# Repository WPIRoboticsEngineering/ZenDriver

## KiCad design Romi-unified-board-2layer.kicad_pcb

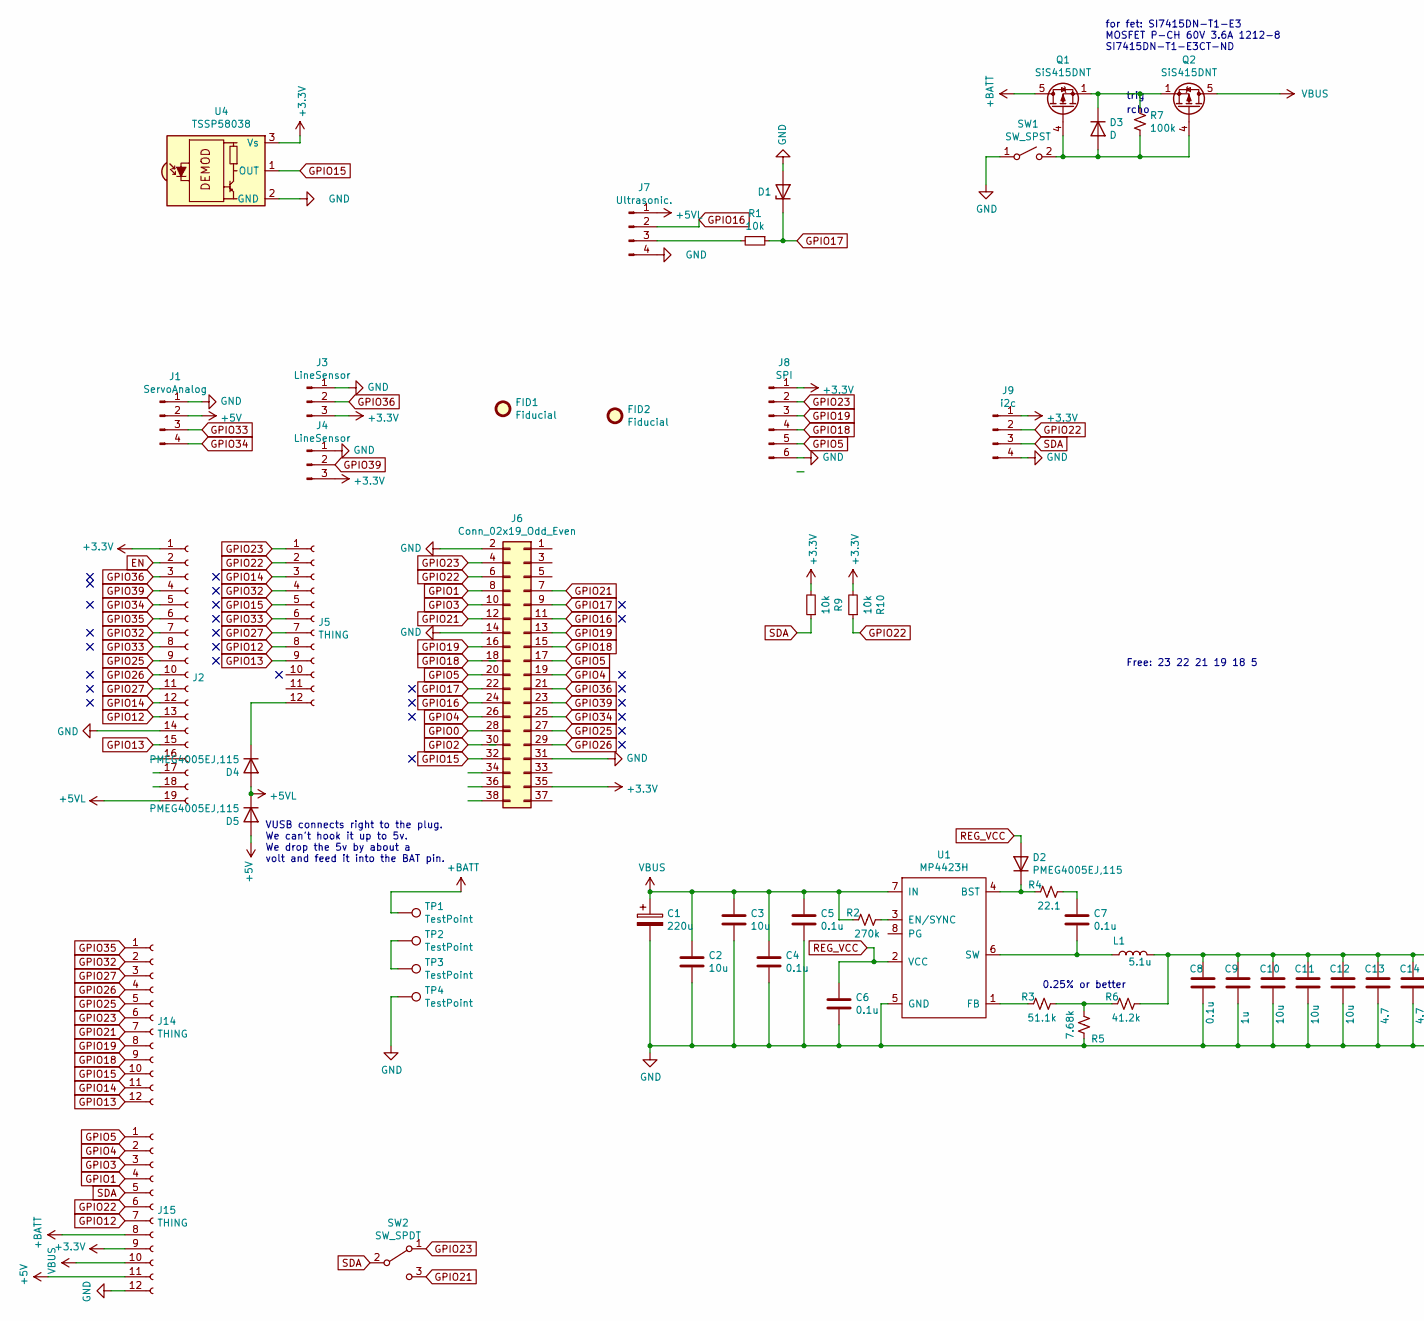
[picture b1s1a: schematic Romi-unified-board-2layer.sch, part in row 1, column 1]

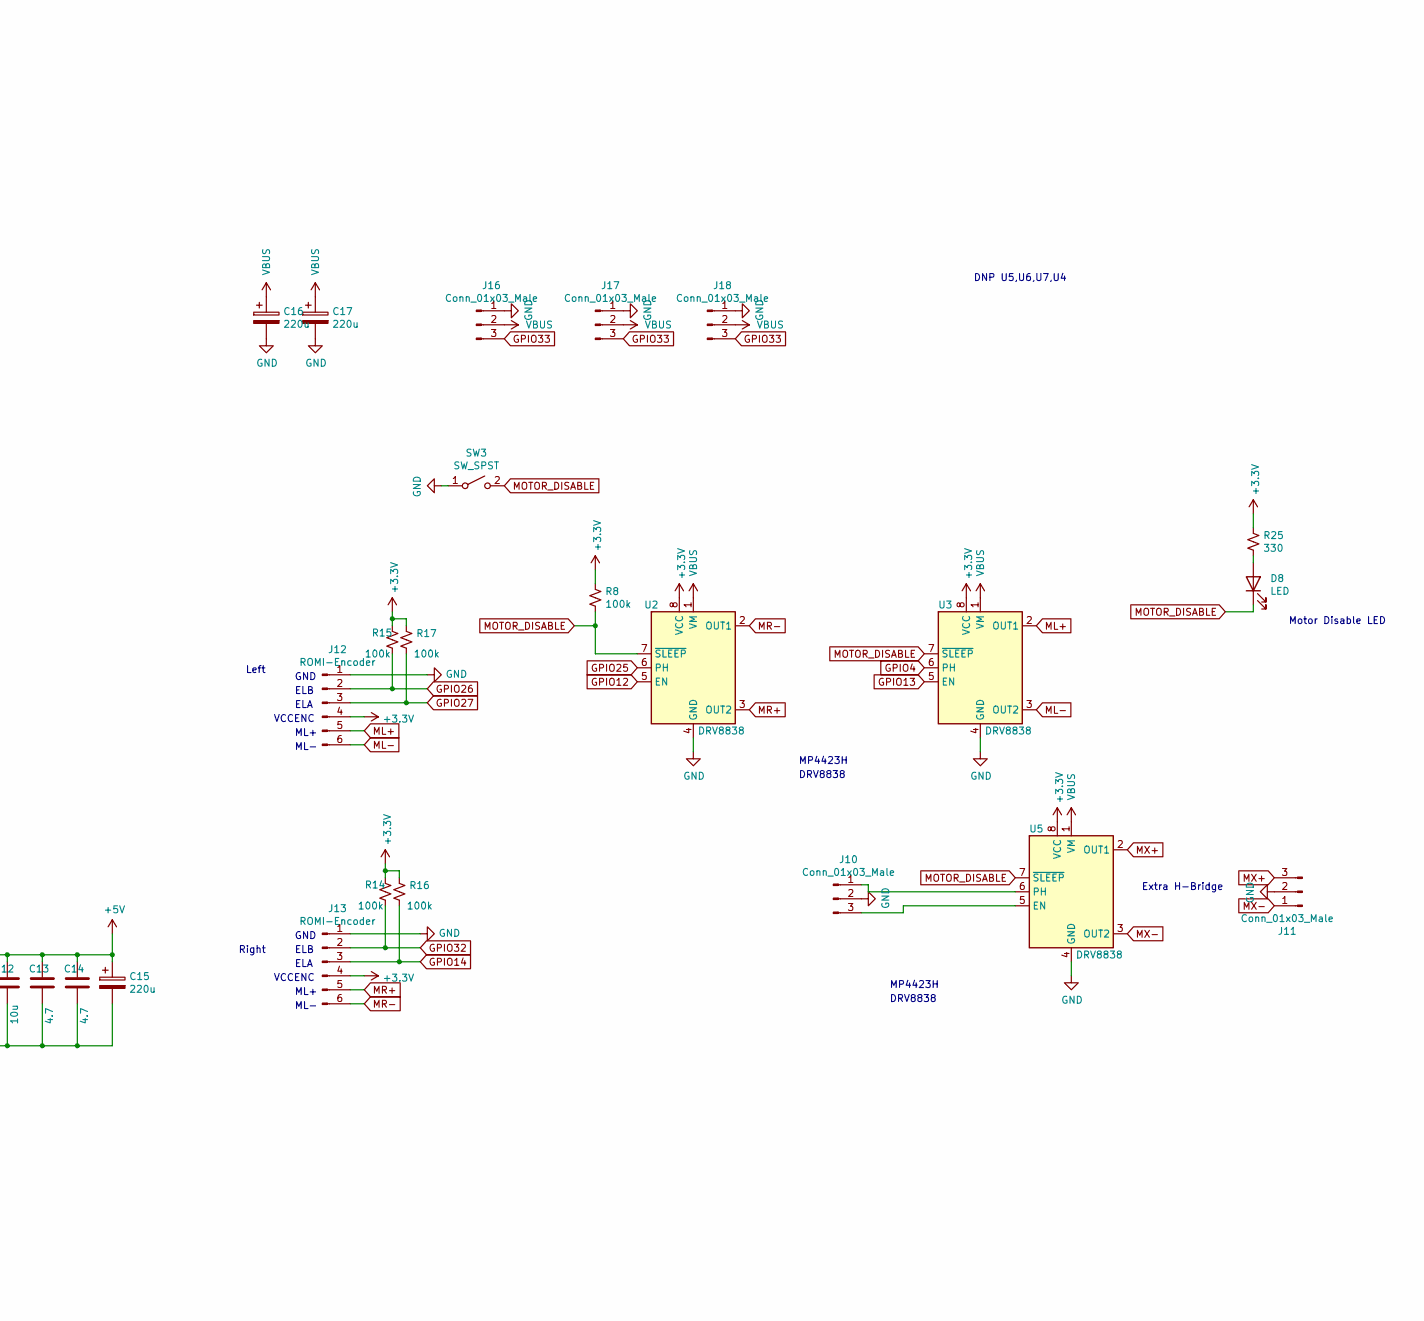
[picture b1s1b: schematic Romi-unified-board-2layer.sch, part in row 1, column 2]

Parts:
C1, C15, C16, C17: 220u; CP_Elec_6.3x3.9
C2, C3, C10, C11, C12: 10u; C_0603_1608Metric
C4, C5, C6, C7, C8: 0.1u; C_0603_1608Metric
C9: 1u; C_0603_1608Metric
C13, C14: 4.7; C_0603_1608Metric
D1: D_Zener; D_SOD-323F
D2, D4, D5: PMEG4005EJ,115; D_SOD-323F
D3: D; D_SOD-323F
D8: LED; LED_0603_1608Metric
FID1, FID2: Fiducial; Fiducial_1mm_Mask2mm
J1: ServoAnalog; PinSocket_1x04_P2.54mm_Vertical
J2: Conn_01x19_Female; PinSocket_1x19_P2.54mm_Vertical
J3, J4: LineSensor; PinSocket_1x03_P2.54mm_Vertical
J5, J14, J15: THING; PinSocket_1x12_P2.54mm_Vertical
J6: Conn_02x19_Odd_Even; PinSocket_2x19_P2.54mm_Vertical
J7: Ultrasonic.; PinSocket_1x04_P2.54mm_Vertical
J8: SPI; PinSocket_1x06_P2.54mm_Vertical
J9: i2c; PinSocket_1x04_P2.54mm_Vertical
J10, J11: Conn_01x03_Male; PinSocket_1x03_P2.54mm_Vertical
J12, J13: ROMI-Encoder; PinSocket_1x06_P2.54mm_Vertical
J16, J17, J18: Conn_01x03_Male; JST_PH_B3B-PH-K_1x03_P2.00mm_Vertical
L1: 5.1u; L_6.3x6.3_H3
Q1, Q2: SiS415DNT; Vishay_PowerPAK_1212-8_Single
R1, R9, R10: 10k; R_0603_1608Metric
R2: 270k; R_0603_1608Metric
R3: 51.1k; R_0603_1608Metric
R4: 22.1; R_0603_1608Metric
R5: 7.68k; R_0603_1608Metric
R6: 41.2k; R_0603_1608Metric
R7, R8, R14, R15, R16, R17: 100k; R_0603_1608Metric
R25: 330; R_0603_1608Metric
SW1, SW3: SW_SPST; SS12D06L5
SW2: SW_SPDT; SS12D06L5
TP1, TP2, TP3, TP4: TestPoint; batterylug
U1: MP4423H
U2, U3, U5: DRV8838; WSON-8-1EP_2x2mm_P0.5mm_EP0.9x1.6mm
U4: TSSP58038; Vishay_MINICAST-3Pin

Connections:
+3V3: J2.1, J3.3, J4.3, J6.35, J8.1, J9.1, J12.4, J13.4, J15.9, R8.1, R9.2, R10.2, R14.1, R15.1, R16.1, R17.1, R25.1, U2.8 (VCC), U3.8 (VCC), U4.3 (Vs), U5.8 (VCC)
+5V: C8.1, C9.1, C10.1, C11.1, C12.1, C13.1, C14.1, C15.1, D5.2 (A), J1.2, J15.11, L1.2, R6.1
+5VL: D4.2 (A), D5.1 (K), J2.19, J7.1
+BATT: J15.8, Q1.5 (D), TP1.1
EN: J2.2
GPIO0: J6.28
GPIO1: J6.8, J15.4
GPIO2: J6.30
GPIO3: J6.10, J15.3
GPIO4: J6.19, J6.26, J15.2, U3.6 (PH)
GPIO5: J6.17, J6.20, J8.5, J15.1
GPIO12: J2.13, J5.8, J15.7, U2.5 (EN)
GPIO13: J2.15, J5.9, J14.12, U3.5 (EN)
GPIO14: J2.12, J5.3, J13.3, J14.11, R16.2
GPIO15: J5.5, J6.32, J14.10, U4.1 (OUT)
GPIO16: J6.11, J6.24, J7.2
GPIO17: D1.1 (K), J6.9, J6.22, R1.1
GPIO18: J6.15, J6.18, J8.4, J14.9
GPIO19: J6.13, J6.16, J8.3, J14.8
GPIO21: J6.7, J6.12, J14.7, SW2.3 (C)
GPIO22: J5.2, J6.6, J9.2, J15.6, R10.1
GPIO23: J5.1, J6.4, J8.2, J14.6, SW2.1 (A)
GPIO25: J2.9, J6.27, J14.5, U2.6 (PH)
GPIO26: J2.10, J6.29, J12.2, J14.4, R15.2
GPIO27: J2.11, J5.7, J12.3, J14.3, R17.2
GPIO32: J2.7, J5.4, J13.2, J14.2, R14.2
GPIO33: J1.3, J2.8, J5.6, J16.3, J17.3, J18.3
GPIO34: J1.4, J2.5, J6.25
GPIO35: J2.6, J14.1
GPIO36: J2.3, J3.2, J6.21
GPIO39: J2.4, J4.2, J6.23
ML+: J12.5, U3.2 (OUT1)
ML-: J12.6, U3.3 (OUT2)
MOTOR_DISABLE: D8.1 (K), R8.2, SW3.2 (B), U2.7 (~SLEEP), U3.7 (~SLEEP), U5.7 (~SLEEP)
MR+: J13.5, U2.3 (OUT2)
MR-: J13.6, U2.2 (OUT1)
MX+: J11.3, U5.2 (OUT1)
MX-: J11.1, U5.3 (OUT2)
unnamed: C7.1, R4.1
unnamed: C7.2, L1.1, U1.6 (SW)
unnamed: D2.1 (K), R4.2, U1.4 (BST)
unnamed: D3.1 (K), Q1.1 (S), Q1.2 (S), Q1.3 (S), Q2.1 (S), Q2.2 (S), Q2.3 (S), R7.1
unnamed: D3.2 (A), Q1.4 (G), Q2.4 (G), R7.2, SW1.2 (B)
unnamed: D4.1 (K), J5.12
unnamed: D8.2 (A), R25.2
unnamed: J7.3, R1.2
unnamed: J10.3, U5.5 (EN)
unnamed: R2.1, U1.3 (EN/SYNC)
unnamed: R3.1, R5.2, R6.2
unnamed: R3.2, U1.1 (FB)
unnamed: TP2.1, TP3.1
REG_VCC: C6.1, D2.2 (A), U1.2 (VCC)
SDA: J9.3, J15.5, R9.1, SW2.2 (B)
VBUS: C1.1, C2.1, C3.1, C4.1, C5.1, C16.1, C17.1, J15.10, J16.2, J17.2, J18.2, Q2.5 (D), R2.2, U1.7 (IN), U2.1 (VM), U3.1 (VM), U5.1 (VM)

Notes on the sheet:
MP4423H
DRV8838
for fet: SI7415DN-T1-E3 MOSFET P-CH 60V 3.6A 1212-8 SI7415DN-T1-E3CT-ND
0.25% or better
GND
ELB
ELA
VCCENC
ML+
ML-
ELA
trig
rcho
Left
Right
Free: 23 22 21 19 18 5
VUSB connects right to the plug. We can't hook it up to 5v. We drop the 5v by about a volt and feed it into the BAT pin.
DNP U5,U6,U7,U4
Motor Disable LED
Extra H-Bridge

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
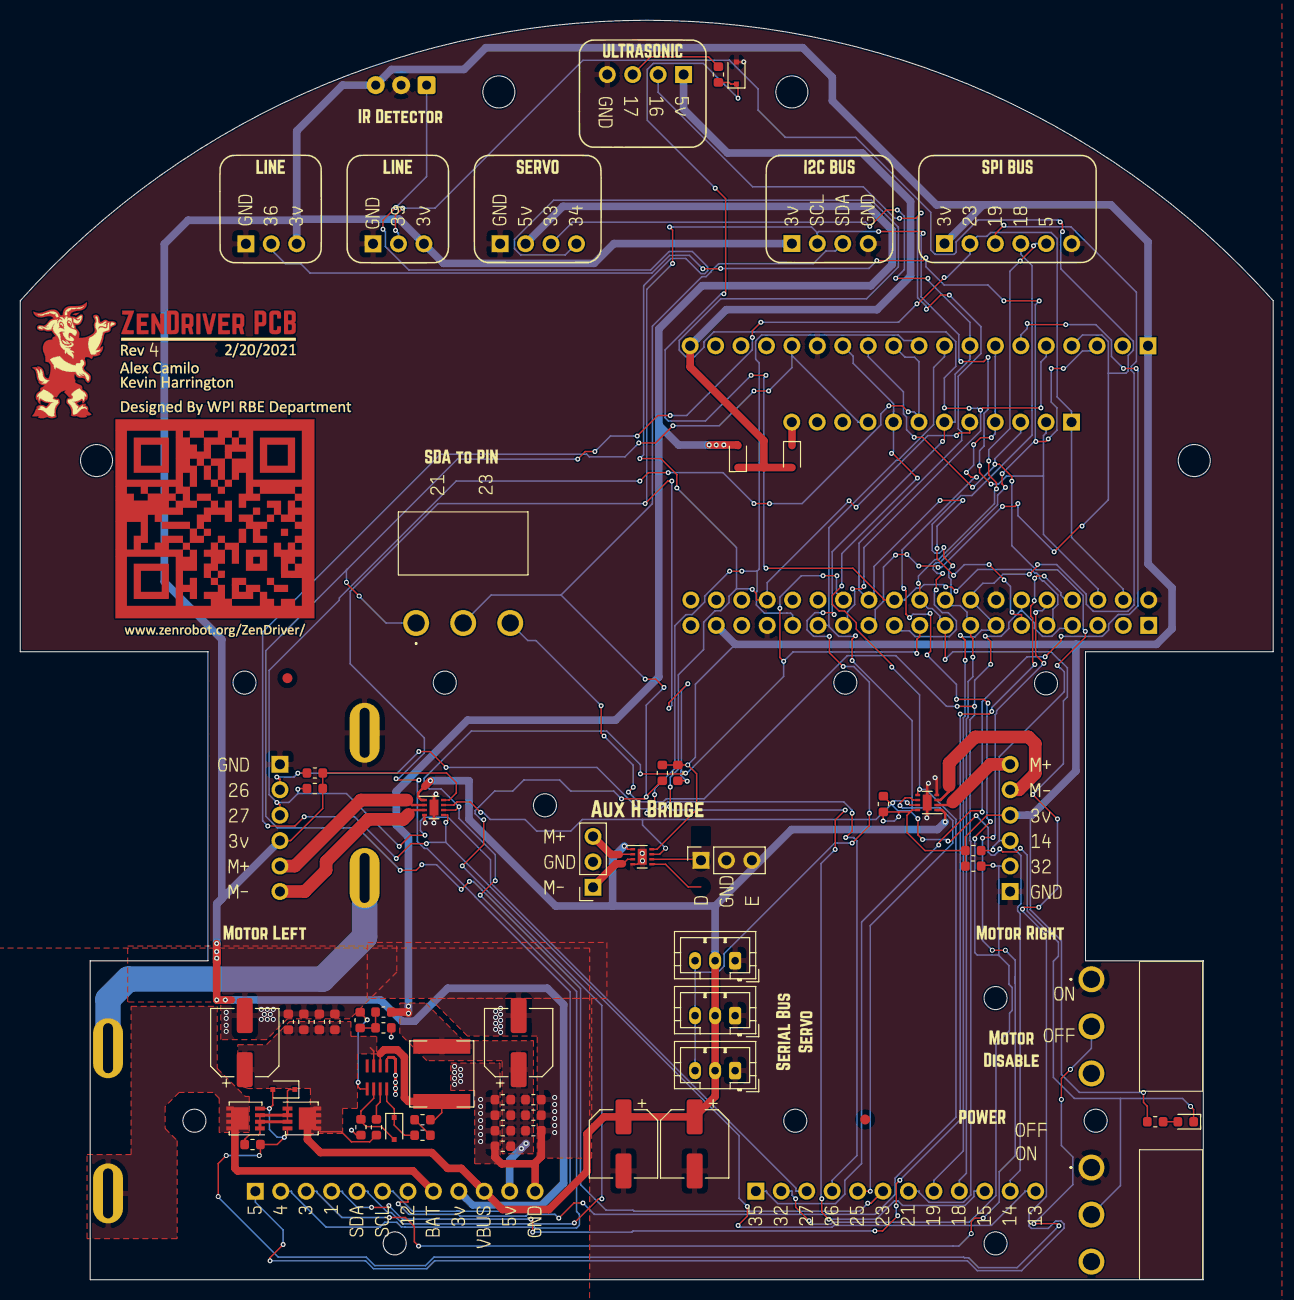
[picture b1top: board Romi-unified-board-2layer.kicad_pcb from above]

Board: 4 copper layers, 125.1 x 125.8 mm, 75 parts (0 on the bottom side), 53 nets.

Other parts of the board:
Ref**: Val**; Romi-unified-board-F_Cu-rev4
Ref**#2: Val**; AuxHBridgeLabel

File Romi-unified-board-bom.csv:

Reference,, Quantity, Value,, Footprint, Datasheet,
C1 C15 C16 C17,565-2206-1-ND ,2,"220u",565-2206-1-ND ,"Capacitor_SMD:CP_Elec_6.3x3.9","~",
C13 C14 ,1276-1784-1-ND,2,"4.7",1276-1784-1-ND,"Capacitor_SMD:C_0603_1608Metric","~",
C3 C10 C11 C12 C2 ,311-1822-1-ND,5,"10u",311-1822-1-ND,"Capacitor_SMD:C_0603_1608Metric","~",
C4 C5 C6 C7 C8 C21 ,1276-1005-1-ND,6,"0.1u",1276-1005-1-ND,"Capacitor_SMD:C_0603_1608Metric","~",
C9 ,1276-1946-1-ND,1,"1u",1276-1946-1-ND,"Capacitor_SMD:C_0603_1608Metric","~",
D1 ,1727-5150-1-ND,1,"D_Zener",1727-5150-1-ND,"Diode_SMD:D_SOD-323F","~",
D2 D4 D5 ,1727-3877-1-ND,3,"PMEG4005EJ,1727-3877-1-ND,115","Diode_SMD:D_SOD-323F","~"
D3 ,1727-3877-1-ND,1,"D",1727-3877-1-ND,"Diode_SMD:D_SOD-323F","~",
D8 ,732-4978-1-ND,1,"LED",732-4978-1-ND,"LED_SMD:LED_0603_1608Metric","~",
J1 ,2057-PH1-04-UA-ND,1,"ServoAnalog",2057-PH1-04-UA-ND,"Connector_PinSocket_2.54mm:PinSocket_1x04_P2.54mm_Vertical","~",
J10 ,455-1568-1-ND,1,"LIDAR_DATA",455-1568-1-ND,"unified:JST_BM06B-GHS-TBT(LF)(SN)(N)","~",
J11 ,455-2650-1-ND,1,"LIDAR_MOTOR",455-2650-1-ND,"unified:JST_SM02B-PASS-TBT(LF)(SN)","~",
J12 J13 ,2057-PH1-06-UA-ND,2,"ROMI-Encoder",2057-PH1-06-UA-ND,"Connector_PinSocket_2.54mm:PinSocket_1x06_P2.54mm_Vertical","~",
J2 ,PPTC191LFBN-RC,1,"Conn_01x19_Female",PPTC191LFBN-RC,,"~",
J4 J3 ,S7036-ND,2,"LineSensor",S7036-ND,"Connector_PinSocket_2.54mm:PinSocket_1x03_P2.54mm_Vertical","~",
J5 J14 J15 ,S7045-ND,3,"THING",S7045-ND,"Connector_PinSocket_2.54mm:PinSocket_1x12_P2.54mm_Vertical","~",
J6 ,PPPC192LFBN-RC,1,"Conn_02x19_Odd_Even",PPPC192LFBN-RC,"Connector_PinSocket_2.54mm:PinSocket_2x19_P2.54mm_Vertical","~",
J7 ,2057-PH1-04-UA-ND,1,"Ultrasonic.",2057-PH1-04-UA-ND,"Connector_PinSocket_2.54mm:PinSocket_1x04_P2.54mm_Vertical","~",
J8 ,S7039-ND,1,"SPI",S7039-ND,"Connector_PinSocket_2.54mm:PinSocket_1x06_P2.54mm_Vertical","~",
J9 ,S7037-ND,1,"i2c",S7037-ND,"Connector_PinSocket_2.54mm:PinSocket_1x04_P2.54mm_Vertical","~",
L1 ,490-10812-1-ND,1,"5.1u",490-10812-1-ND,"Inductor_SMD:L_6.3x6.3_H3","~",
Q2 Q1 ,SI7415DN-T1-E3CT-ND,2,"SiS415DNT",SI7415DN-T1-E3CT-ND,"Package_SO:Vishay_PowerPAK_1212-8_Single","https://www.vishay.com/docs/63684/sis415dnt.pdf",
R1 R9 R10 ,RNCP0603FTD10K0CT-ND,3,"10k",RNCP0603FTD10K0CT-ND,"Resistor_SMD:R_0603_1608Metric","~",
R2 ,13-RT0603FRE07270KLCT-ND,1,"270k",13-RT0603FRE07270KLCT-ND,"Resistor_SMD:R_0603_1608Metric","~",
R25 ,RMCF0603JT330RCT-ND,1,"330",RMCF0603JT330RCT-ND,"Resistor_SMD:R_0603_1608Metric","~",
R3 ,P51.1KBNCT-ND,1,"51.1k",P51.1KBNCT-ND,"Resistor_SMD:R_0603_1608Metric","~",
R4 ,311-22.1HRCT-ND,1,"22.1",311-22.1HRCT-ND,"Resistor_SMD:R_0603_1608Metric","~",
R5 ,738-RMCF0603FT7K68CT-ND,1,"7.68k",738-RMCF0603FT7K68CT-ND,"Resistor_SMD:R_0603_1608Metric","~",
R6 ,RMCF0603FT41K2CT-ND,1,"41.2k",RMCF0603FT41K2CT-ND,"Resistor_SMD:R_0603_1608Metric","~",
R7 R8 R17 R15 R16 R14 ,RMCF0603FG100KCT-ND,6,"100k",RMCF0603FG100KCT-ND,"Resistor_SMD:R_0603_1608Metric","~",
SW1 ,563-1091-1-ND,1,"SW_SPST",563-1091-1-ND,"unified:CSS-1210TB","~",
SW2 ,563-1091-1-ND,1,"SW_SPDT",563-1091-1-ND,"unified:CSS-1210TB","~",
U1 ,1589-1664-1-ND,1,"MP4423H",1589-1664-1-ND,"Package_DFN_QFN:DFN-8-1EP_3x3mm_P0.65mm_EP1.7x2.05mm","",
U3 U2 ,296-37539-1-ND,2,"DRV8838",296-37539-1-ND,"Package_SON:WSON-8-1EP_2x2mm_P0.5mm_EP0.9x1.6mm","http://www.ti.com/lit/ds/symlink/drv8837.pdf",
U5,497-15996-1-ND,1,LSM6DS33TR ,497-15996-1-ND,,,
U4,TSSP58038-ND,1,TSSP58038,TSSP58038-ND,,,

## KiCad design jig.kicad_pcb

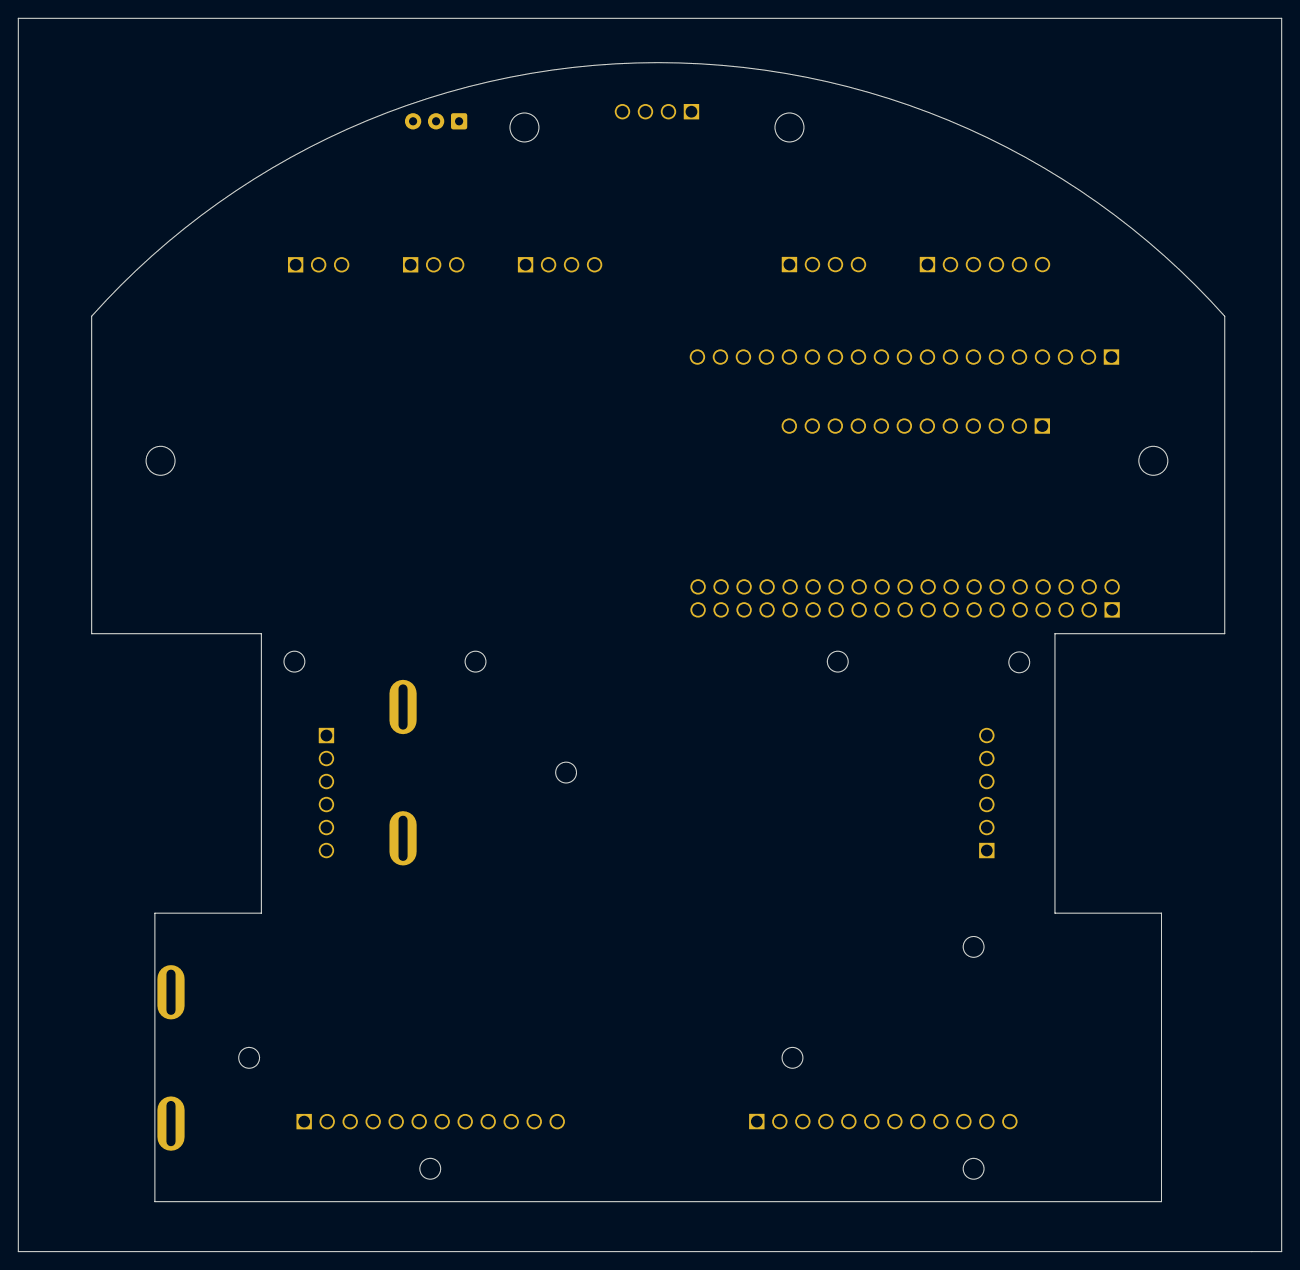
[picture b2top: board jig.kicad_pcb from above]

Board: 4 copper layers, 139.5 x 136.2 mm, 18 parts (0 on the bottom side), 31 nets, no tracks yet.

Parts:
J1: ServoAnalog; PinSocket_1x04_P2.54mm_Vertical
J2: Conn_01x19_Female; PinSocket_1x19_P2.54mm_Vertical
J3, J4: LineSensor; PinSocket_1x03_P2.54mm_Vertical
J5, J14, J15: THING; PinSocket_1x12_P2.54mm_Vertical_1_3mm
J6: Conn_02x19_Odd_Even; PinSocket_2x19_P2.54mm_Vertical
J7: Ultrasonic.; PinSocket_1x04_P2.54mm_Vertical
J8: SPI; PinSocket_1x06_P2.54mm_Vertical_1_3mm
J9: i2c; PinSocket_1x04_P2.54mm_Vertical
J12, J13: ROMI-Encoder; PinSocket_1x06_P2.54mm_Vertical_1_3mm
TP1, TP2, TP3, TP4: TestPoint; batterylug
U4: TSSP58038; Vishay_MINICAST-3Pin

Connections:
+3V3: J2.1, J3.3, J4.3, J6.35, J8.1, J9.1, J12.4, J13.4, J15.9, U4.3
+5V: J1.2, J15.11
+5VL: J2.19, J7.1
+BATT: J15.8, TP1.1
GND: J1.1, J2.14, J3.1, J4.1, J6.2, J6.14, J6.31, J7.4, J8.6, J9.4, J12.1, J13.1, J15.12, TP4.1, U4.2
GPIO1: J6.8, J15.4
GPIO3: J6.10, J15.3
GPIO4: J6.19, J6.26, J15.2
GPIO5: J6.17, J6.20, J8.5, J15.1
GPIO12: J2.13, J5.8, J15.7
GPIO13: J2.15, J5.9, J14.12
GPIO14: J2.12, J5.3, J13.3, J14.11
GPIO15: J5.5, J6.32, J14.10, U4.1
GPIO16: J6.11, J6.24, J7.2
GPIO17: J6.9, J6.22
GPIO18: J6.15, J6.18, J8.4, J14.9
GPIO19: J6.13, J6.16, J8.3, J14.8
GPIO21: J6.7, J6.12, J14.7
GPIO22: J5.2, J6.6, J9.2, J15.6
GPIO23: J5.1, J6.4, J8.2, J14.6
GPIO25: J2.9, J6.27, J14.5
GPIO26: J2.10, J6.29, J12.2, J14.4
GPIO27: J2.11, J5.7, J12.3, J14.3
GPIO32: J2.7, J5.4, J13.2, J14.2
GPIO33: J1.3, J2.8, J5.6
GPIO34: J1.4, J2.5, J6.25
GPIO35: J2.6, J14.1
GPIO36: J2.3, J3.2, J6.21
GPIO39: J2.4, J4.2, J6.23
unnamed: TP2.1, TP3.1
SDA: J9.3, J15.5

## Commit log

2020-09-22 Layout done, Beginning work on silk.
2020-10-08 Re-routed board
    Resolved issues #6 and #5
2020-10-09 Advanced board with IO muxing
2020-10-09 minor updates
2020-10-11 Finished schematic
2020-10-13 back traces away from holes.
2020-10-13 flipped ultrasonic, removed IO2 from j8
2020-10-13 Added silk.
2020-10-13 Fixed DRC errors, generated gerbers.
2020-10-25 generated BOM
2020-10-27 Changes for rev2
    rotated Q2
    Fixed too-thin trace in DC-DC Circuit.
    Created correct footprint for U1. No 9th pad.
2020-10-27 Motor Disable is now a physical switch.
    #7
2020-10-29 Rev2
    Added smart servo connectors
    Added IR sensor
    Updated silk label
2020-10-29 More rev2 changes
    Fixed inductor FP
    Swapped out accelerometer with an in stock variant.
2020-10-29 clean up accel schematic
2020-10-29 Widen Battery tab footprints
2020-10-29 Added ir sensor to bom
2020-10-29 added fiducials
2020-10-29 Create PCBWay-BOM.xls
    pcbway formatted BOM
2020-10-30 Fixed error in netlist.
2020-10-30 Swapped pins 16 and 17
    #10
2020-10-30 Trace edit.
2020-10-30 Fixed ultrasonic
    #10
2020-11-01 Batch of changes
    Fixed Switch footprint
    Swapped left and right H bridges to match shim.
    Updated silkscreen
    Fixed ultrasonic pinout.
2020-11-01 Updated Silkscreen
2020-11-02 Minor Changes
    Updated switch part.
    Removed LIDAR connector and IMU.
2020-11-11 Swapped right motor -+
    #18
2020-11-11 Update switch footprint.
2020-11-24 updated gitignore, fixed plot settings
2020-11-26 Make unwanted silkscreen features invisable.
2020-12-18 Added jig PCB
2020-12-18 libraries for jig PCB
2020-12-18 Pin diagram, incomplete.
    Artwork layout/style done, some of the values are correct.
2021-01-28 Create ZenDriver-Pinouts.svg
    Pinouts for esp32 and feather/samd51
2021-01-29 Fixed error in SPI pins
    #32
2021-03-24 Rev 4
